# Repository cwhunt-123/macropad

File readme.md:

# HackPad Project by Collin Hunt

## Screenshots

## Description

Project Description:
This project is a custom-designed, 9-key mechanical macropad featuring a rotary encoder, powered by a Seeed Studio XIAO RP2040 microcontroller. It utilizes a custom-designed printed circuit board (PCB) to wire the MX-style switches and diodes, all housed within a custom designed 3d-printed case.

How to Use It:
Once flashed with the compatible QMK keyboard firmware, simply connect the macropad to your computer via USB. You can press the mechanical keys to trigger your own personalized shortcuts, scripts, or macros, and use the rotary encoder for continuous adjustments like volume control, zooming, or timeline scrubbing.

Why I Made It:
I built this macropad primarily as a hands-on learning experience to dive into custom hardware design from scratch. It served as the perfect practical project to teach myself how to design and route my own PCBs, as well as how to use CAD software to model a functional, precise 3D-printed case to fit my electronics.

## BOM

 - 1x Seeed Studio XIAO RP2040
 - 1x EC11 Rotary Encoder
 - 9x MX-Style Switches
 - 9x 1N4148 Diodes
 - 4x M3x5mx4mm
 - 4x M3x16mm Screws
 - 9x White Blank DSA Keycaps
 - 1x 3D Printed Case

https://cad.onshape.com/documents/48a17990b1831c041b00876b/w/f84d6e38766eb00843111f91/e/a30079d502902473d825c4da?renderMode=0&uiState=69cec4f78e56fd57fc233f29 

## Thank you!! :)

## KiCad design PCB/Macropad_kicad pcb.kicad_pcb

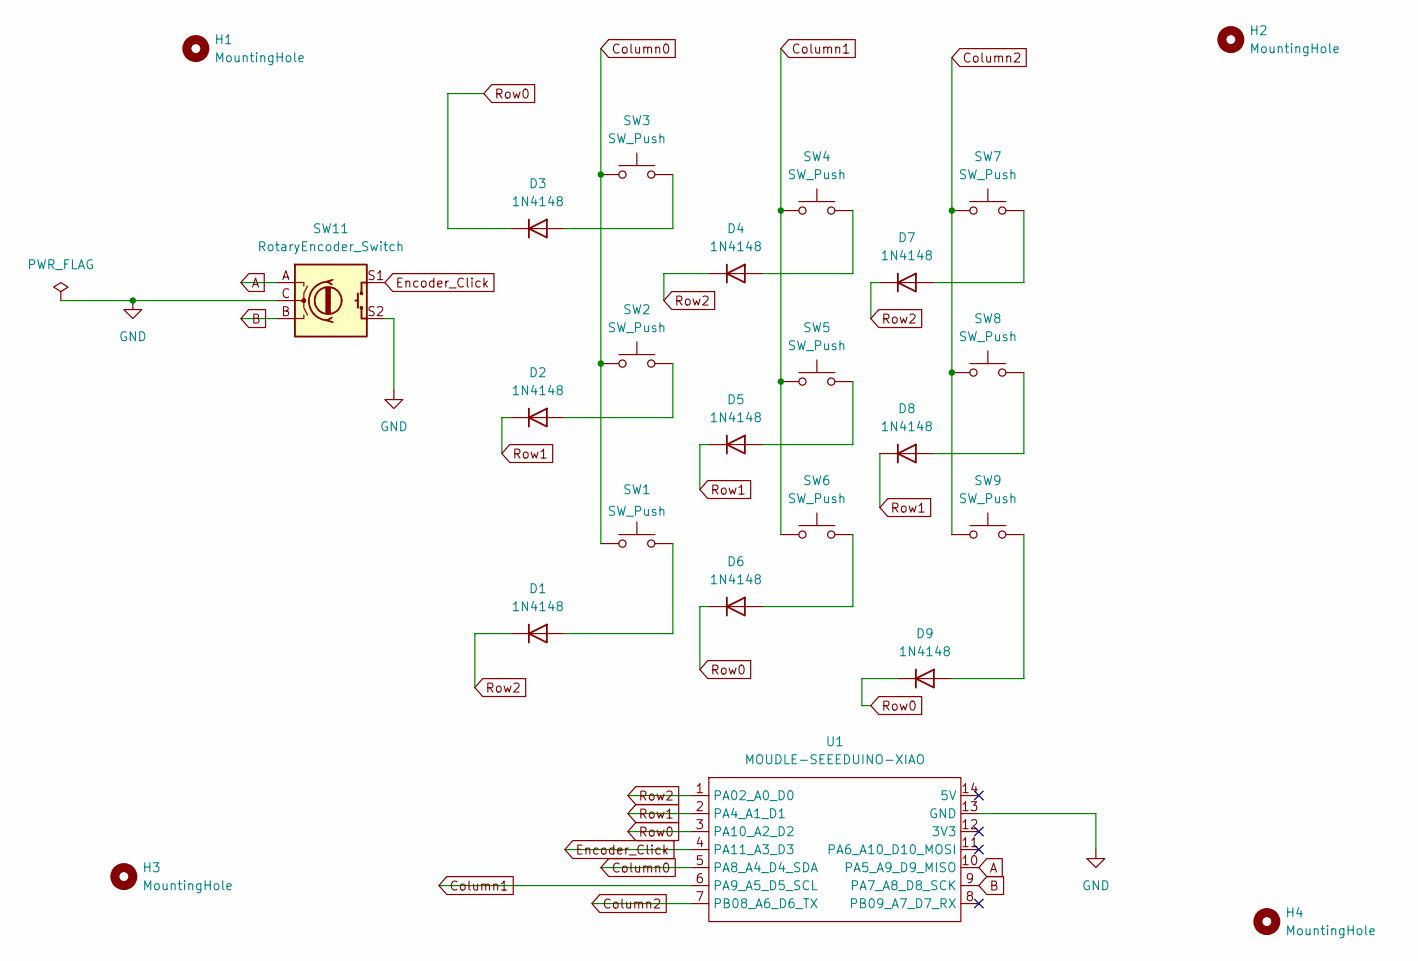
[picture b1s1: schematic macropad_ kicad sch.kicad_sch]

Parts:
D1, D2, D3, D4, D5, D6, D7, D8, D9: 1N4148; D_DO-35_SOD27_P7.62mm_Horizontal
H1, H2, H3, H4: MountingHole; MountingHole_3.2mm_M3
SW1, SW2, SW3, SW4, SW5, SW6, SW7, SW8, SW9: SW_Push; SW_Cherry_MX_1.00u_PCB
SW11: RotaryEncoder_Switch; RotaryEncoder_Alps_EC12E-Switch_Vertical_H20mm
U1: MOUDLE-SEEEDUINO-XIAO; XIAO-Generic-Hybrid-14P-2.54-21X17.8MM

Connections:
A: SW11.A, U1.10 (PA5_A9_D9_MISO)
B: SW11.B, U1.9 (PA7_A8_D8_SCK)
Column0: SW1.1, SW2.1, SW3.1, U1.5 (PA8_A4_D4_SDA)
Column1: SW4.1, SW5.1, SW6.1, U1.6 (PA9_A5_D5_SCL)
Column2: SW7.1, SW8.1, SW9.1, U1.7 (PB08_A6_D6_TX)
Encoder_Click: SW11.S1, U1.4 (PA11_A3_D3)
GND: SW11.C, SW11.S2, U1.13 (GND)
unnamed: D1.2 (A), SW1.2
unnamed: D2.2 (A), SW2.2
unnamed: D3.2 (A), SW3.2
unnamed: D4.2 (A), SW4.2
unnamed: D5.2 (A), SW5.2
unnamed: D6.2 (A), SW6.2
unnamed: D7.2 (A), SW7.2
unnamed: D8.2 (A), SW8.2
unnamed: D9.2 (A), SW9.2
Row0: D3.1 (K), D6.1 (K), D9.1 (K), U1.3 (PA10_A2_D2)
Row1: D2.1 (K), D5.1 (K), D8.1 (K), U1.2 (PA4_A1_D1)
Row2: D1.1 (K), D4.1 (K), D7.1 (K), U1.1 (PA02_A0_D0)

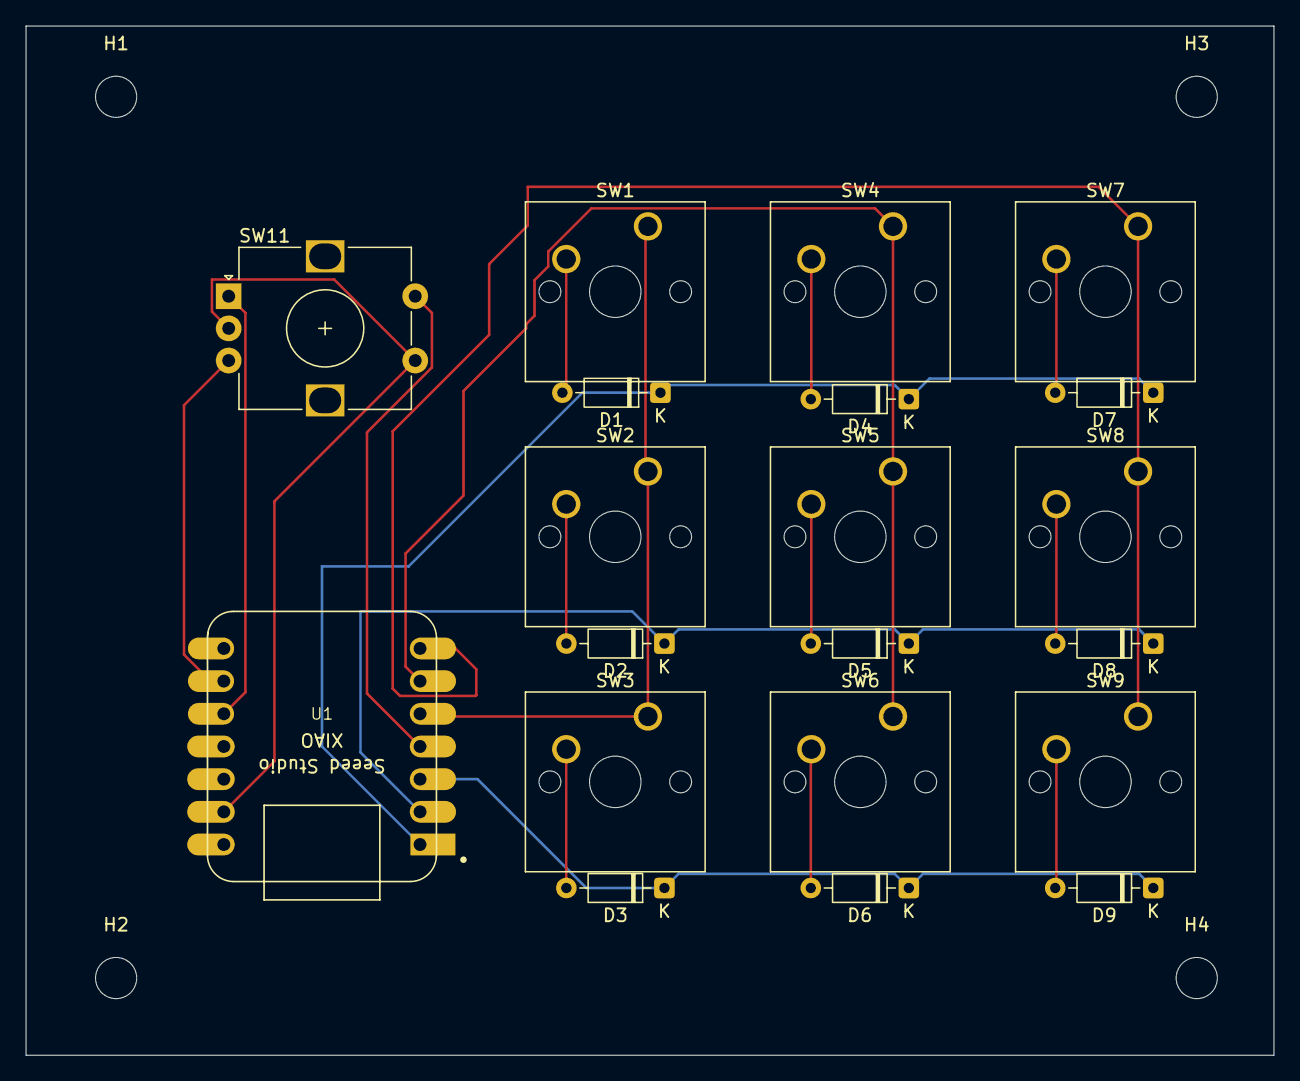
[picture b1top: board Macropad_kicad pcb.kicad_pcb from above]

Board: 2 copper layers, 97.0 x 80.0 mm, 24 parts (0 on the bottom side), 19 nets.

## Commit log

2026-04-01 Upload
